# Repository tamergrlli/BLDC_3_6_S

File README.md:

# BLDC_3_6_S — Open-Source 3S–6S Sensorless BLDC Motor Driver

An open-source three-phase BLDC motor driver for 3S–6S lithium battery packs,
designed in KiCad 10. It targets sensorless six-step control using back-EMF
zero-crossing detection, with a single-shunt current sense and a hardware
over-current trip.

> **Status: work in progress.** The schematic and PCB layout are complete and
> DRC-clean; the design is in final review. The board has **not** been manufactured or tested yet. Do not order
> boards from this revision — see [Known issues](#known-issues--todo).

## Key features

| Block | Implementation |
|---|---|
| Input | 3S–6S Li-ion (≈ 9–25.2 V), SMBJ33CA TVS, polyfuse + Schottky reverse protection for the auxiliary supply |
| Power stage | 6 × TI CSD18540Q5B (60 V, SON 5×6), 2 × 22 µF ceramic per half-bridge, 2 × 330 µF bulk at the input |
| Gate driver | TI DRV8300, 12 V gate drive, separate turn-on / turn-off gate resistors |
| Current sense | 1 mΩ single DC-link shunt + INA181 (bus current, not per-phase), TLV7011 comparator wired to TIM1_BRK for a fast hardware over-current trip, 1.8 V reference (MCP1700) |
| Sensorless feedback | Per-phase back-EMF dividers with RC filter and BAT54S clamps, virtual neutral, DC-bus voltage sense |
| MCU | STM32F103R8T6, 8 MHz crystal, 5-pin SWD header with NRST, 32 Mbit SPI flash (W25Q32JV) |
| Supplies | SEPIC (LM5022) → 12 V gate drive, TPS54302 buck → 5 V, AP2112K → 3.3 V |
| Communication | CAN (TJA1042) on a Molex Micro-Fit 3.0 connector, jumper-selectable 120 Ω termination |
| User I/O | UART debug header (USART3, JST-EH), speed potentiometer, external 0–5 V analog speed input with a 5 V supply pin, 3 status LEDs, 2 push-buttons with RC debounce |
| Monitoring & debug | 12 V gate-drive rail sense, 17 test points (supply rails, BEMF, neutral, current sense, over-current trip, SPI) |
| PCB | 4 layers, 1 oz copper, 90 × 70 mm, solder-wire pads for battery (4 mm²) and motor phases (2.5 mm²) |

**Why a SEPIC?** The gate driver needs a stable 12 V rail, but a 3S pack can sag
below 12 V while a 6S pack sits well above it. A SEPIC can step up or down, so
one supply covers the whole 3S–6S range.

**Design target:** around 30 A phase current. This is a target, not a measured
value; thermal and current capability have not been verified on hardware.

## Images

| Top (3D) | Bottom (3D) |
|---|---|
|  |  |

Top copper and silkscreen: [docs/images/layout_top.png](docs/images/layout_top.png)
Schematic (PDF): [docs/BLDC_3_6_S_schematic.pdf](docs/BLDC_3_6_S_schematic.pdf)

## Repository layout

```
BLDC_3_6_S/            KiCad 10 project (schematic, PCB, design rules)
bldc_lib/symbols/      Project symbol library (DRV8300, TLV7011)
bldc_lib/3dmodels/     Vendor 3D models (not included, see README inside)
docs/                  Renders and schematic PDF
```

All project libraries are referenced relative to the project
(`${KIPRJMOD}/../bldc_lib/...`), so the design opens on any machine with
KiCad 10 and its standard libraries. Only the J4 connector's vendor 3D model has
to be downloaded separately — see [bldc_lib/3dmodels/README.md](bldc_lib/3dmodels/README.md).

## MCU pin notes

- Status LEDs: D1 on PB4, D2 on PB3, D3 on PD2.
- PB3 and PB4 are JTAG pins after reset. The firmware must disable JTAG and
  keep SWD only (CubeMX: *SYS → Debug = Serial Wire*), otherwise D1 and D2
  will not work.

## Planned hardware additions

- NTC next to the low-side MOSFETs for thermal protection
- ESD protection on the CAN bus
- RC-PWM (servo-style) speed input on a timer-capable pin, alongside the analog input

## Known issues / TODO

- [x] Move the 5 V buck switch node off the inner layer onto the top layer
- [x] Finish routing (MCU analog inputs, PWM pull-downs, SPI flash, SWD, remaining GND / 3.3 V connections)
- [ ] Route each high-side gate trace together with its phase (SH) return to shrink the gate loop
- [ ] Connect the SEPIC MOSFET snubber
- [x] Sync capacitor footprints between schematic and PCB (C28, C75, C77, C78, C80, C81 and C23, C24)
- [x] DRC clean (only silkscreen warnings remain)
- [ ] Clear ERC warnings (no-connect flags on unused MCU pins, PWR_FLAGs)
- [ ] Review copper weight (1 oz vs 2 oz) for continuous high-current operation
- [x] Add UART, speed inputs, status LEDs, push-buttons, 12 V rail sense and test points
- [ ] Add an NTC next to the power stage for thermal protection

## Roadmap

1. Finish the remaining hardware additions, complete layout, clean ERC / DRC
2. First prototype and bring-up
3. Firmware: sensorless six-step commutation with BEMF zero-crossing detection
4. Characterisation: current capability, thermals, efficiency

The board measures DC-link current only, so it is aimed at six-step control.
Field-oriented control would need per-phase current: either single-shunt
phase-current reconstruction (with a faster current-sense amplifier) or a
future hardware revision with per-phase shunts.

## Contributing

Feedback, design reviews and issues are very welcome — especially on the power
stage layout, the sensorless front end and the gate-drive loop. Please open an
issue or a pull request.

## License

This hardware design is licensed under the
**CERN Open Hardware Licence Version 2 – Strongly Reciprocal (CERN-OHL-S-2.0)**.
See [LICENSE](LICENSE) for the full text.

Copyright © 2026 tamergrlli

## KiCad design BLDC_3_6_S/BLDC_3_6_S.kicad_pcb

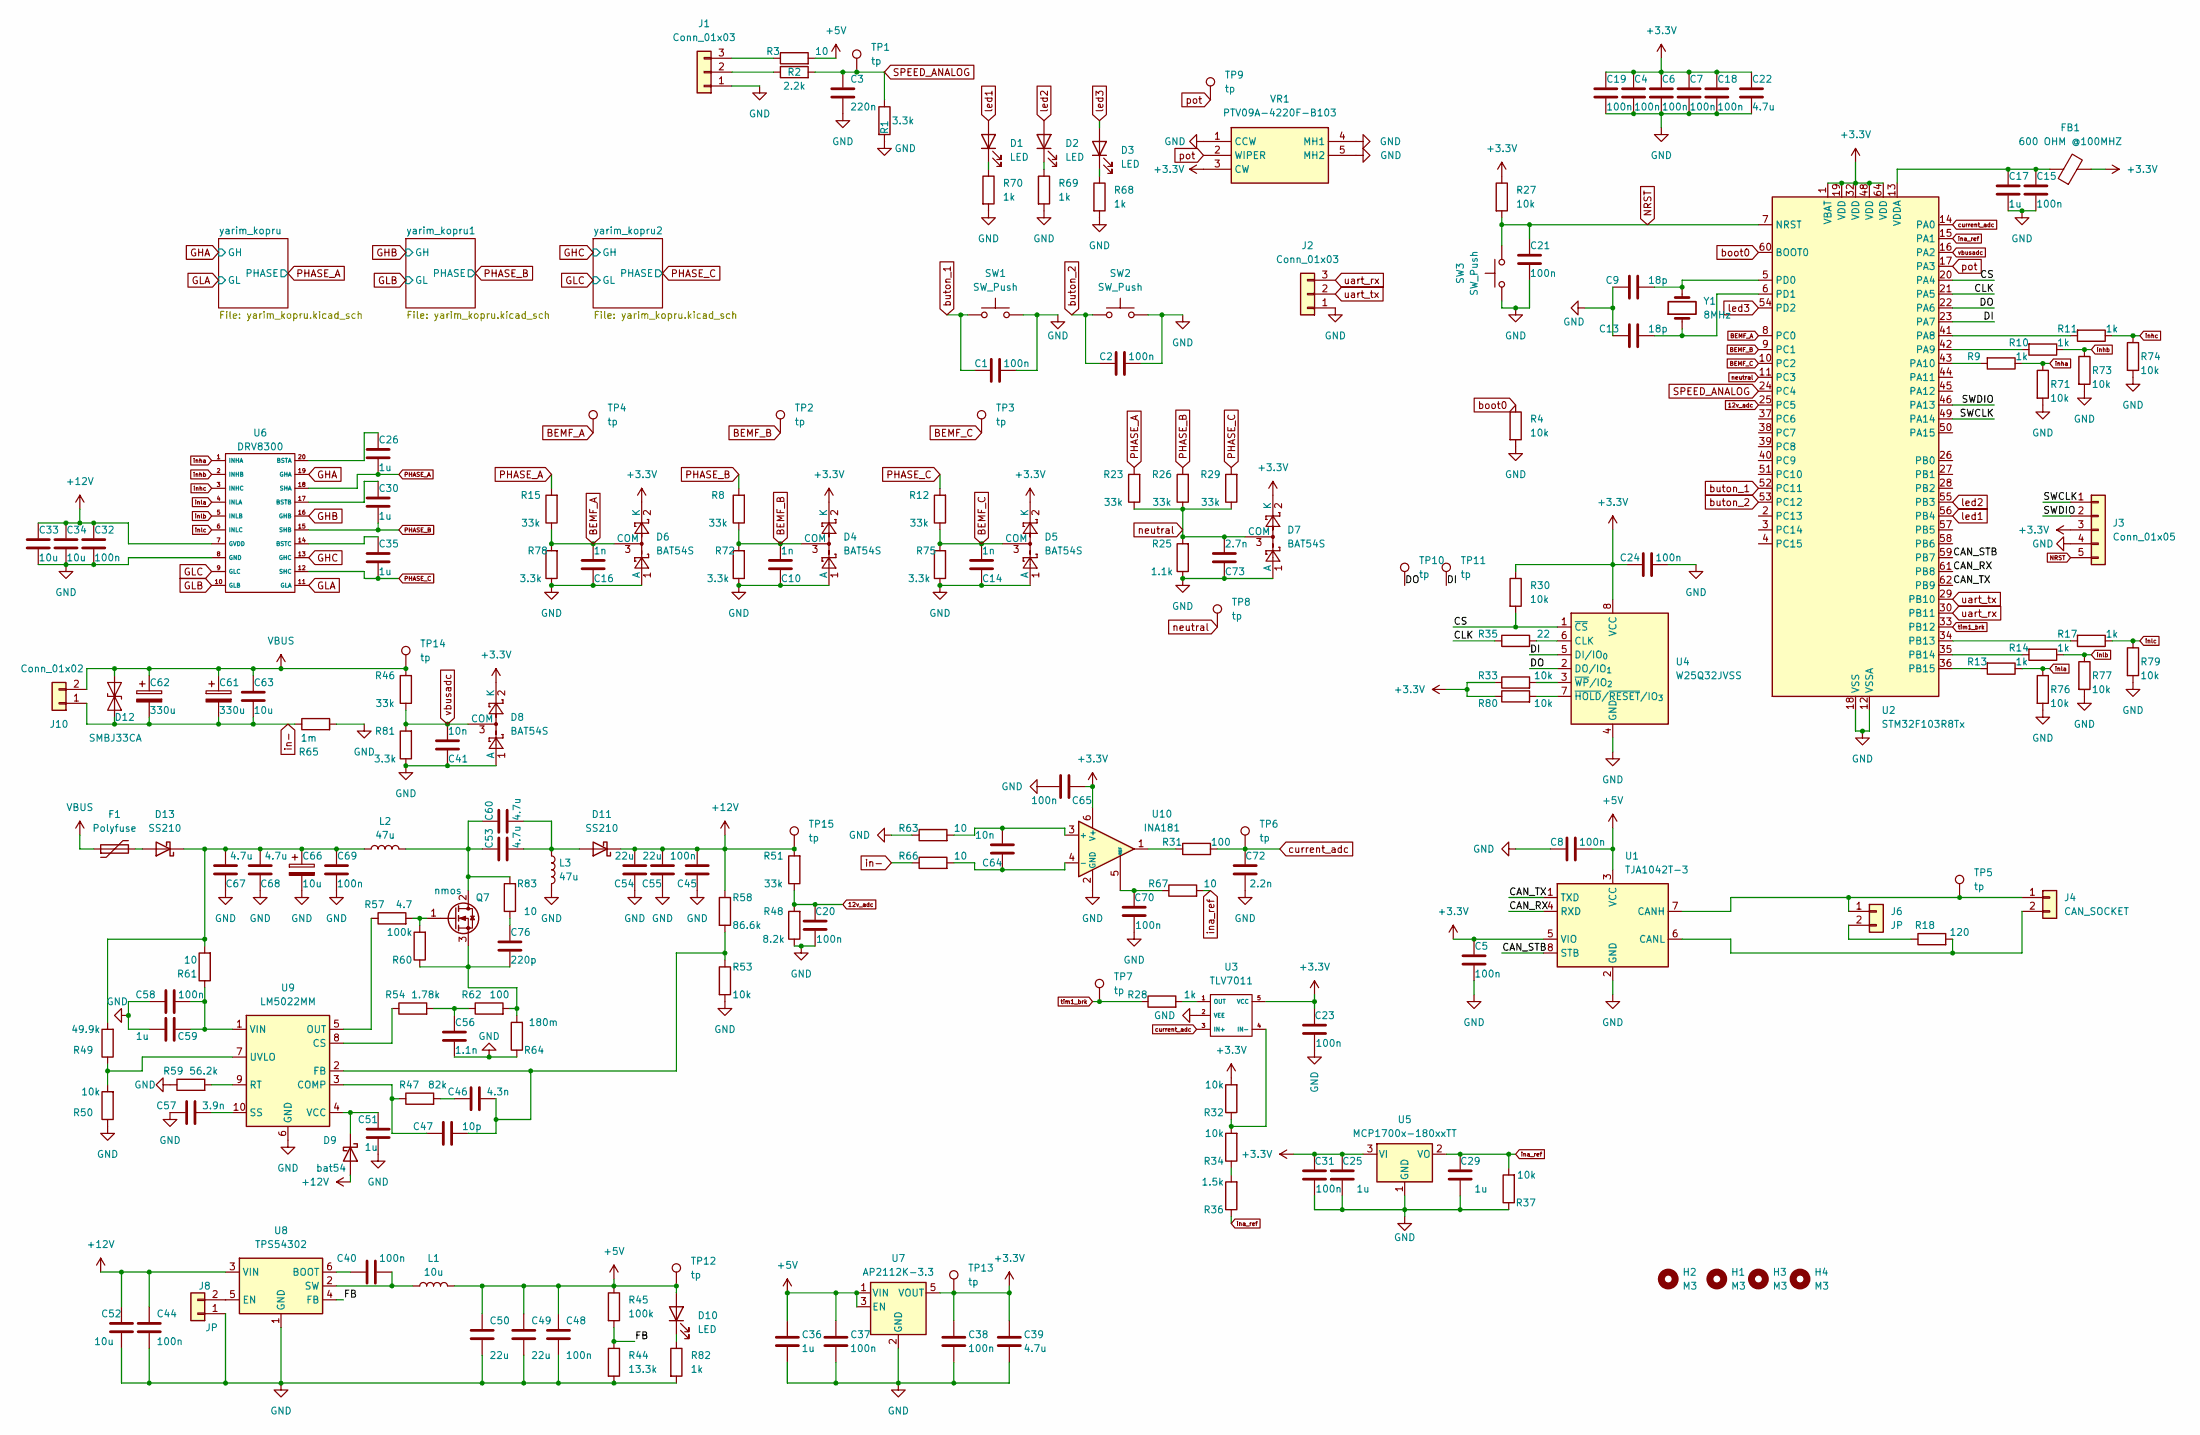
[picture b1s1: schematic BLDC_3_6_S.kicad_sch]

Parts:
C1, C2, C4, C5, C6, C7, C8, C15, C18, C19, C20, C21, C23, C24, C31, C37, C38, C45, C58, C65, C69, C70: 100n; C_0603_1608Metric
C3: 220n; C_0603_1608Metric
C9, C13: 18p; C_0603_1608Metric
C10, C14, C16: 1n; C_0603_1608Metric
C17, C25, C29: 1u; C_0603_1608Metric
C22, C39: 4.7u; C_1206_3216Metric
C26, C30, C35, C36, C51, C59: 1u; C_0805_2012Metric
C32, C40, C44, C48: 100n; C_0805_2012Metric
C33, C34: 10u; C_1210_3225Metric
C41, C64: 10n; C_0603_1608Metric
C46: 4.3n; C_0603_1608Metric
C47: 10p; C_0603_1608Metric
C49, C50: 22u; C_1206_3216Metric
C52, C63: 10u; C_1206_3216Metric
C53, C60, C67, C68: 4.7u; C_1210_3225Metric
C54, C55: 22u; C_1210_3225Metric
C56: 1.1n; C_0603_1608Metric
C57: 3.9n; C_0603_1608Metric
C61, C62: 330u; CP_Elec_10x10.5
C66: 10u; CP_Elec_6.3x5.3
C72: 2.2n; C_0603_1608Metric
C73: 2.7n; C_0603_1608Metric
C76: 220p; C_0603_1608Metric
D1, D2, D3, D10: LED; LED_0805_2012Metric
D4, D5, D6, D7, D8: BAT54S; SOT-23
D9: bat54; D_SOD-123
D11, D13: SS210; D_SMA
D12: SMBJ33CA; D_SMB
F1: Polyfuse; R_1812_4532Metric
FB1: 600 OHM @100MHZ; L_0805_2012Metric
H1, H2, H3, H4: M3; MountingHole_3.2mm_M3_ISO7380
J1, J2: Conn_01x03; JST_EH_B3B-EH-A_1x03_P2.50mm_Vertical
J3: Conn_01x05; PinHeader_1x05_P2.54mm_Vertical
J4: CAN_SOCKET; Molex_Micro-Fit_3.0_43650-0200_1x02_P3.00mm_Horizontal
J6, J8: JP; PinHeader_1x02_P1.27mm_Vertical
J10: Conn_01x02; SolderWire-4sqmm_1x02_P12mm_D3mm_OD6mm
L1: 10u; L_Bourns-SRN4018
L2, L3: 47u; L_Bourns_SRR1260
Q7: nmos; TO-252-2
R1, R72, R75, R78, R81: 3.3k; R_0603_1608Metric
R2: 2.2k; R_0603_1608Metric
R3, R61, R63, R66, R67, R83: 10; R_0603_1608Metric
R4, R27, R30, R32, R33, R34, R37, R50, R53, R71, R73, R74, R76, R77, R79, R80: 10k; R_0603_1608Metric
R8, R12, R15, R23, R26, R29, R46, R51: 33k; R_0603_1608Metric
R9, R10, R11, R13, R14, R17, R28: 1k; R_0603_1608Metric
R18: 120; R_0603_1608Metric
R25: 1.1k; R_0603_1608Metric
R31, R62: 100; R_0603_1608Metric
R35: 22; R_0805_2012Metric
R36: 1.5k; R_0603_1608Metric
R44: 13.3k; R_0805_2012Metric
R45: 100k; R_0805_2012Metric
R47: 82k; R_0603_1608Metric
R48: 8.2k; R_0603_1608Metric
R49: 49.9k; R_0603_1608Metric
R54: 1.78k; R_0603_1608Metric
R57: 4.7; R_0603_1608Metric
R58: 86.6k; R_0603_1608Metric
R59: 56.2k; R_0603_1608Metric
R60: 100k; R_0603_1608Metric
R64: 180m; R_1206_3216Metric
R65: 1m; R_2512_6332Metric
R68, R69, R70, R82: 1k; R_0805_2012Metric
SW1, SW2, SW3: SW_Push; SW_Push_1P1T_NO_CK_KMR2
TP1, TP2, TP3, TP4, TP5, TP6, TP7, TP8, TP9, TP10, TP11, TP12, TP13, TP14, TP15: tp; TestPoint_Pad_D1.5mm
U1: TJA1042T-3; SOIC-8_3.9x4.9mm_P1.27mm
U2: STM32F103R8Tx; LQFP-64_10x10mm_P0.5mm
U3: TLV7011; SOT-23-5
U4: W25Q32JVSS; SOIC-8_5.3x5.3mm_P1.27mm
U5: MCP1700x-180xxTT; SOT-23
U6: DRV8300; TSSOP-20_4.4x6.5mm_P0.65mm
U7: AP2112K-3.3; SOT-23-5
U8: TPS54302; SOT-23-6
U9: LM5022MM; MSOP-10_3x3mm_P0.5mm
U10: INA181; SOT-23-6
VR1: PTV09A-4220F-B103; PTV09A4220FB103; Mouser Part Number 652-PTV09A-4220FB103
Y1: 8MHz; Crystal_SMD_5032-2Pin_5.0x3.2mm

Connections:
12v_adc: C20.2, R48.2, R51.1, U2.25 (PC5)
+3.3V: C4.2, C5.1, C6.2, C7.2, C18.2, C19.2, C22.2, C23.2, C24.1, C25.2, C31.2, C38.2, C39.1, C65.2, D4.2 (K), D5.2 (K), D6.2 (K), D7.2 (K), D8.2 (K), FB1.2, J3.3, R27.1, R30.1, R32.2, R33.1, R80.1, TP13.1 (1_1), U1.5 (VIO), U2.1 (VBAT), U2.19 (VDD), U2.32 (VDD), U2.48 (VDD), U2.64 (VDD), U3.5 (VCC), U4.8 (VCC), U5.3 (VI), U7.5 (VOUT), U10.6 (V+), VR1.3 (CW)
+5V: C8.2, C36.1, C37.2, C48.1, C49.1, C50.1, D10.2 (A), L1.2, R3.2, R45.1, TP12.1 (1_1), U1.3 (VCC), U7.1 (VIN), U7.3 (EN)
+12V: C32.1, C33.1, C34.1, C44.1, C45.1, C52.1, C54.2, C55.2, D9.2 (A), D11.1 (K), R51.2, R58.1, TP15.1 (1_1), U6.7 (GVDD), U8.3 (VIN)
/CAN_RX: U1.4 (RXD), U2.61 (PB8)
/CAN_STB: U1.8 (STB), U2.59 (PB7)
/CAN_TX: U1.1 (TXD), U2.62 (PB9)
/CLK: R35.1, U2.21 (PA5)
/CS: R30.2, U2.20 (PA4), U4.1 (~CS)
/DI: TP11.1 (1_1), U2.23 (PA7), U4.5 (DI/IO_{0})
/DO: TP10.1 (1_1), U2.22 (PA6), U4.2 (DO/IO_{1})
/FB: R44.1, R45.2, U8.4 (FB)
/SWCLK: J3.1, U2.49 (PA14)
/SWDIO: J3.2, U2.46 (PA13)
BEMF_A: C16.1, D6.3 (COM), R15.1, R78.2, TP4.1 (1_1), U2.8 (PC0)
BEMF_B: C10.1, D4.3 (COM), R8.1, R72.2, TP2.1 (1_1), U2.9 (PC1)
BEMF_C: C14.1, D5.3 (COM), R12.1, R75.2, TP3.1 (1_1), U2.10 (PC2)
GHA: U6.19 (GHA); also elsewhere on the board
GHB: U6.16 (GHB); also elsewhere on the board
GHC: U6.13 (GHC); also elsewhere on the board
GLA: U6.11 (GLA); also elsewhere on the board
GLB: U6.10 (GLB); also elsewhere on the board
GLC: U6.9 (GLC); also elsewhere on the board
GND: C1.2, C2.2, C3.2, C4.1, C5.2, C6.1, C7.1, C8.1, C9.1, C10.2, C13.1, C14.2, C15.1, C16.2, C17.1, C18.1, C19.1, C20.1, C21.2, C22.1, C23.1, C24.2, C25.1, C29.1, C31.1, C32.2, C33.2, C34.2, C36.2, C37.1, C38.1, C39.2, C41.2, C44.2, C45.2, C48.2, C49.2, C50.2, C51.2, C52.2, C54.1, C55.1, C56.2, C57.1, C58.1, C59.2, C65.1, C66.2, C67.1, C68.1, C69.2, C70.1, C72.1, C73.2, D4.1 (A), D5.1 (A), D6.1 (A), D7.1 (A), D8.1 (A), J1.1, J2.1, J3.4, J8.1, L3.2, R1.2, R4.2, R25.1, R37.1, R44.2, R48.1, R50.1, R53.2, R59.1, R63.1, R64.1, R65.2, R68.2, R69.2, R70.2, R71.2, R72.1, R73.2, R74.2, R75.1, R76.2, R77.2, R78.1, R79.2, R81.1, R82.2, SW1.2, SW2.2, SW3.1, U1.2 (GND), U2.12 (VSSA), U2.18 (VSS), U2.31 (VSS), U2.47 (VSS), U2.63 (VSS), U3.2 (VEE), U4.4 (GND), U5.1 (GND), U6.8 (GND), U7.2 (GND), U8.1 (GND), U9.6 (GND), U10.2 (GND), VR1.1 (CCW), VR1.4 (MH1), VR1.5 (MH2); also elsewhere on the board
NRST: C21.1, J3.5, R27.2, SW3.2, U2.7 (NRST)
unnamed: C46.1, R47.2
unnamed: C56.1, R54.2, R62.1
unnamed: C76.1, R83.1
unnamed: D1.1 (K), R70.1
unnamed: D2.1 (K), R69.1
unnamed: D3.1 (K), R68.1
unnamed: C51.1, D9.1 (K), U9.4 (VCC)
unnamed: D10.1 (K), R82.1
unnamed: C53.2, C60.2, D11.2 (A), L3.1
unnamed: D13.2 (A), F1.2
unnamed: C66.1, C67.2, C68.2, C69.1, D13.1 (K), L2.1, R49.2, R61.2
unnamed: J1.2, R2.1
unnamed: J1.3, R3.1
unnamed: J4.1, J6.1, TP5.1 (1_1), U1.7 (CANH)
unnamed: J4.2, R18.2, U1.6 (CANL)
unnamed: J6.2, R18.1
unnamed: J8.2, U8.5 (EN)
unnamed: C53.1, C60.1, L2.2, Q7.2 (D), R83.2
unnamed: Q7.1 (G), R57.2, R60.2
unnamed: C76.2, Q7.3 (S), R60.1, R62.2, R64.2
unnamed: R31.1, U10.1
unnamed: R34.1, R36.2
unnamed: R11.2, U2.41 (PA8)
unnamed: R10.2, U2.42 (PA9)
unnamed: R9.2, U2.43 (PA10)
unnamed: R17.2, U2.34 (PB13)
unnamed: R14.2, U2.35 (PB14)
unnamed: R13.2, U2.36 (PB15)
unnamed: C9.2, U2.5 (PD0), Y1.2
unnamed: C13.2, U2.6 (PD1), Y1.1
unnamed: C15.2, C17.2, FB1.1, U2.13 (VDDA)
unnamed: R32.1, R34.2, U3.4 (IN-)
unnamed: R28.2, U3.1 (OUT)
unnamed: R35.2, U4.6 (CLK)
unnamed: R80.2, U4.7 (~HOLD/~RESET/IO_{3})
unnamed: R33.2, U4.3 (~WP/IO_{2})
unnamed: C26.1, U6.20 (BSTA)
unnamed: C30.1, U6.17 (BSTB)
unnamed: C35.1, U6.14 (BSTC)
unnamed: C40.1, U8.6 (BOOT)
unnamed: C40.2, L1.1, U8.2 (SW)
unnamed: C47.1, R47.1, U9.3 (COMP)
unnamed: R54.1, U9.8 (CS)
unnamed: C46.2, C47.2, R53.1, R58.2, U9.2 (FB)
unnamed: R57.1, U9.5 (OUT)
unnamed: R59.2, U9.9 (RT)
unnamed: C57.2, U9.10 (SS)
unnamed: R49.1, R50.2, U9.7 (UVLO)
unnamed: C58.2, C59.1, R61.1, U9.1 (VIN)
unnamed: C64.1, R63.2, U10.3 (+)
unnamed: C64.2, R66.2, U10.4 (-)
unnamed: C70.2, R67.1, U10.5 (REF)
PHASE_A: C26.2, R15.2, R23.2, U6.18 (SHA); also elsewhere on the board
PHASE_B: C30.2, R8.2, R26.2, U6.15 (SHB); also elsewhere on the board
PHASE_C: C35.2, R12.2, R29.2, U6.12 (SHC); also elsewhere on the board
SPEED_ANALOG: C3.1, R1.1, R2.2, TP1.1 (1_1), U2.24 (PC4)
VBUS: C61.1, C62.1, C63.1, D12.1 (A1), F1.1, J10.2, R46.2, TP14.1 (1_1); also elsewhere on the board
boot0: R4.1, U2.60 (BOOT0)
buton_1: C1.1, SW1.1, U2.52 (PC11)
buton_2: C2.1, SW2.1, U2.53 (PC12)
current_adc: C72.2, R31.2, TP6.1 (1_1), U2.14 (PA0), U3.3 (IN+)
in-: C61.2, C62.2, C63.2, D12.2 (A2), J10.1, R65.1, R66.1
ina_ref: C29.2, R36.1, R37.2, R67.2, U2.15 (PA1), U5.2 (VO)
inha: R9.1, R71.1, U6.1 (INHA)
inhb: R10.1, R73.1, U6.2 (INHB)
inhc: R11.1, R74.1, U6.3 (INHC)
inla: R13.1, R76.1, U6.4 (INLA)
inlb: R14.1, R77.1, U6.5 (INLB)
inlc: R17.1, R79.1, U6.6 (INLC)
led1: D1.2 (A), U2.56 (PB4)
led2: D2.2 (A), U2.55 (PB3)
led3: D3.2 (A), U2.54 (PD2)
neutral: C73.1, D7.3 (COM), R23.1, R25.2, R26.1, R29.1, TP8.1 (1_1), U2.11 (PC3)
pot: TP9.1 (1_1), U2.17 (PA3), VR1.2 (WIPER)
tim1_brk: R28.1, TP7.1 (1_1), U2.33 (PB12)
uart_rx: J2.3, U2.30 (PB11)
uart_tx: J2.2, U2.29 (PB10)
vbusadc: C41.1, D8.3 (COM), R46.1, R81.2, U2.16 (PA2)

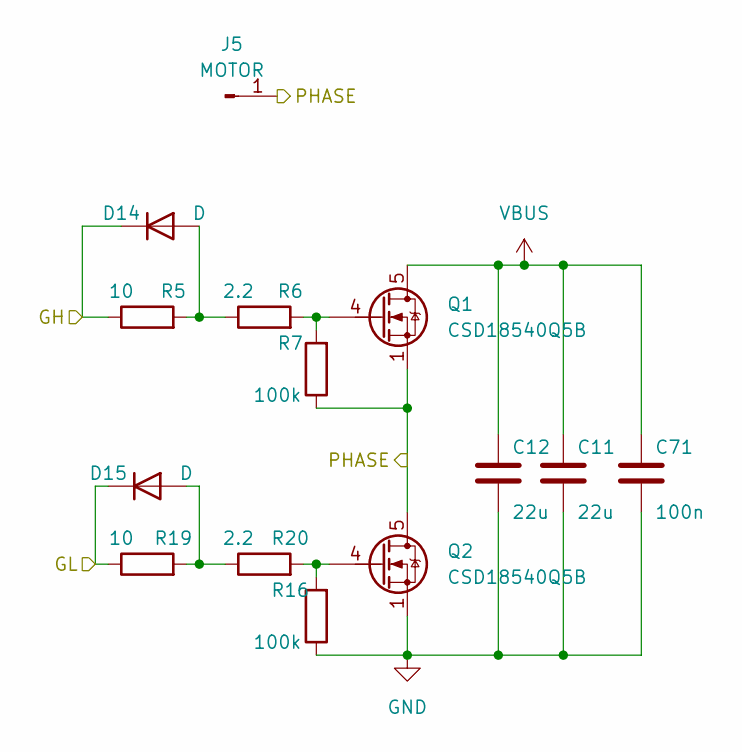
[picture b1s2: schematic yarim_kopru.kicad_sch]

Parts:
C11, C12: 22u; C_1210_3225Metric
C71: 100n; C_0805_2012Metric
D14, D15: D; D_SOD-123
J5: MOTOR; SolderWire-2.5sqmm_1x01_D2.4mm_OD4.4mm
Q1, Q2: CSD18540Q5B; TDSON-8-1
R5, R19: 10; R_0603_1608Metric
R6, R20: 2.2; R_0603_1608Metric
R7, R16: 100k; R_0603_1608Metric

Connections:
GHA: D14.1 (K), R5.1; also elsewhere on the board
GLA: D15.1 (K), R19.1; also elsewhere on the board
GND: C11.2, C12.2, C71.2, Q2.1 (S), Q2.2 (S), Q2.3 (S), R16.1; also elsewhere on the board
unnamed: D14.2 (A), R5.2, R6.1
unnamed: D15.2 (A), R19.2, R20.1
unnamed: Q1.4 (G), R6.2, R7.2
unnamed: Q2.4 (G), R16.2, R20.2
PHASE_A: J5.1 (Pin_1_1), Q1.1 (S), Q1.2 (S), Q1.3 (S), Q2.5 (D), R7.1; also elsewhere on the board
VBUS: C11.1, C12.1, C71.1, Q1.5 (D); also elsewhere on the board

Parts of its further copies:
C27, C28, C42, C43: 22u; C_1210_3225Metric
C74, C75: 100n; C_0805_2012Metric
D16, D17, D18, D19: D; D_SOD-123
J7, J9: MOTOR; SolderWire-2.5sqmm_1x01_D2.4mm_OD4.4mm
Q3, Q4, Q5, Q6: CSD18540Q5B; TDSON-8-1
R21, R39, R41, R55: 10; R_0603_1608Metric
R22, R40, R42, R56: 2.2; R_0603_1608Metric
R24, R38, R43, R52: 100k; R_0603_1608Metric

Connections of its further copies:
GHB: D16.1 (K), R21.1; also elsewhere on the board
GHC: D18.1 (K), R41.1; also elsewhere on the board
GLB: D17.1 (K), R39.1; also elsewhere on the board
GLC: D19.1 (K), R55.1; also elsewhere on the board
GND: C27.2, C28.2, C42.2, C43.2, C74.2, C75.2, Q4.1 (S), Q4.2 (S), Q4.3 (S), Q6.1 (S), Q6.2 (S), Q6.3 (S), R38.1, R52.1; also elsewhere on the board
unnamed: D16.2 (A), R21.2, R22.1
unnamed: D17.2 (A), R39.2, R40.1
unnamed: D18.2 (A), R41.2, R42.1
unnamed: D19.2 (A), R55.2, R56.1
unnamed: Q3.4 (G), R22.2, R24.2
unnamed: Q4.4 (G), R38.2, R40.2
unnamed: Q5.4 (G), R42.2, R43.2
unnamed: Q6.4 (G), R52.2, R56.2
PHASE_B: J7.1 (Pin_1_1), Q3.1 (S), Q3.2 (S), Q3.3 (S), Q4.5 (D), R24.1; also elsewhere on the board
PHASE_C: J9.1 (Pin_1_1), Q5.1 (S), Q5.2 (S), Q5.3 (S), Q6.5 (D), R43.1; also elsewhere on the board
VBUS: C27.1, C28.1, C42.1, C43.1, C74.1, C75.1, Q3.5 (D), Q5.5 (D); also elsewhere on the board

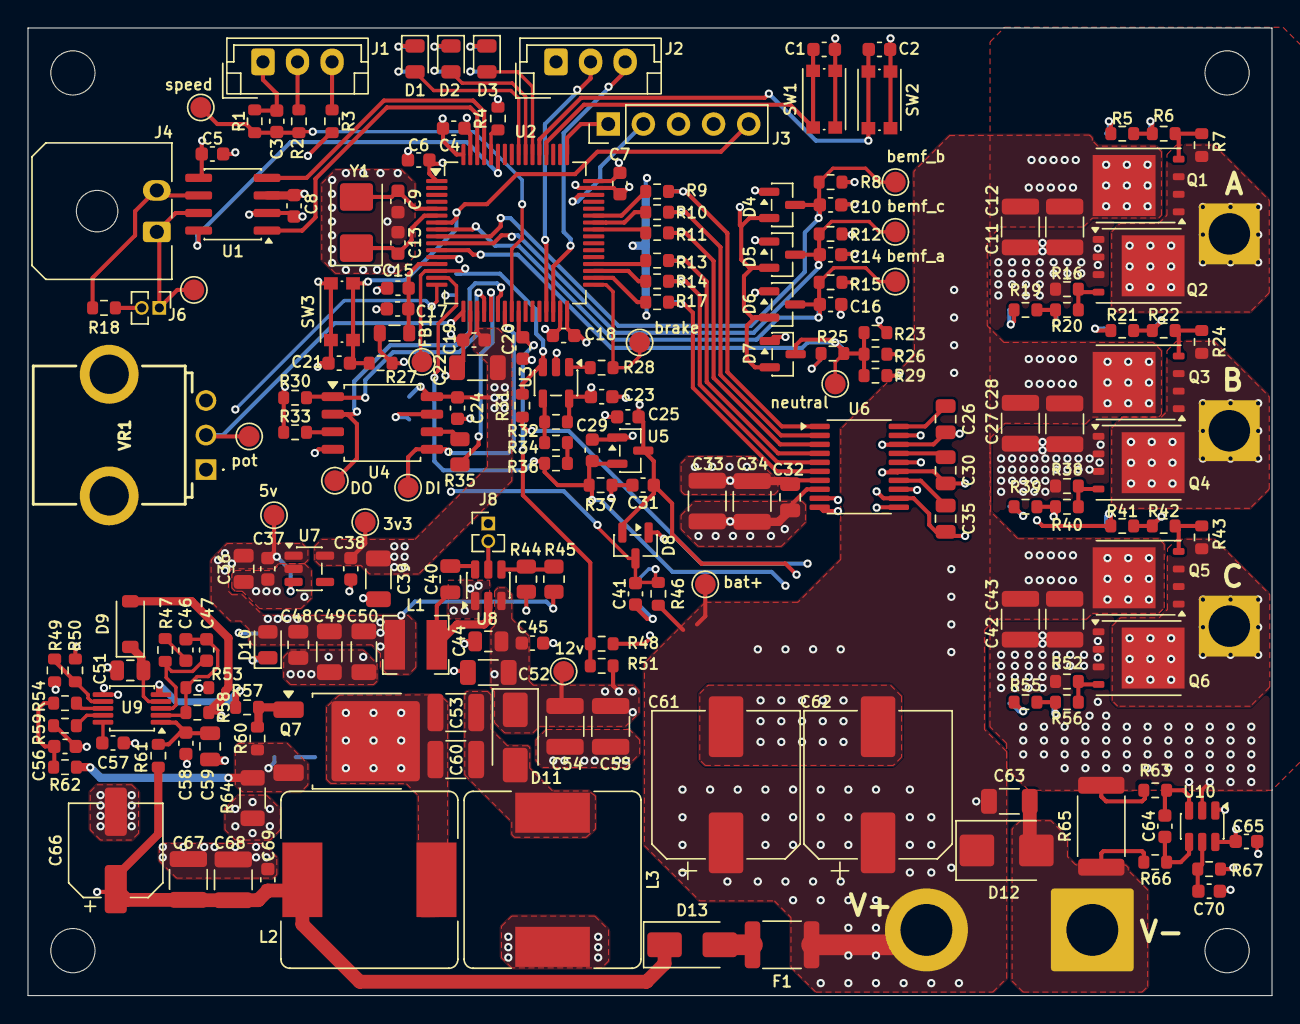
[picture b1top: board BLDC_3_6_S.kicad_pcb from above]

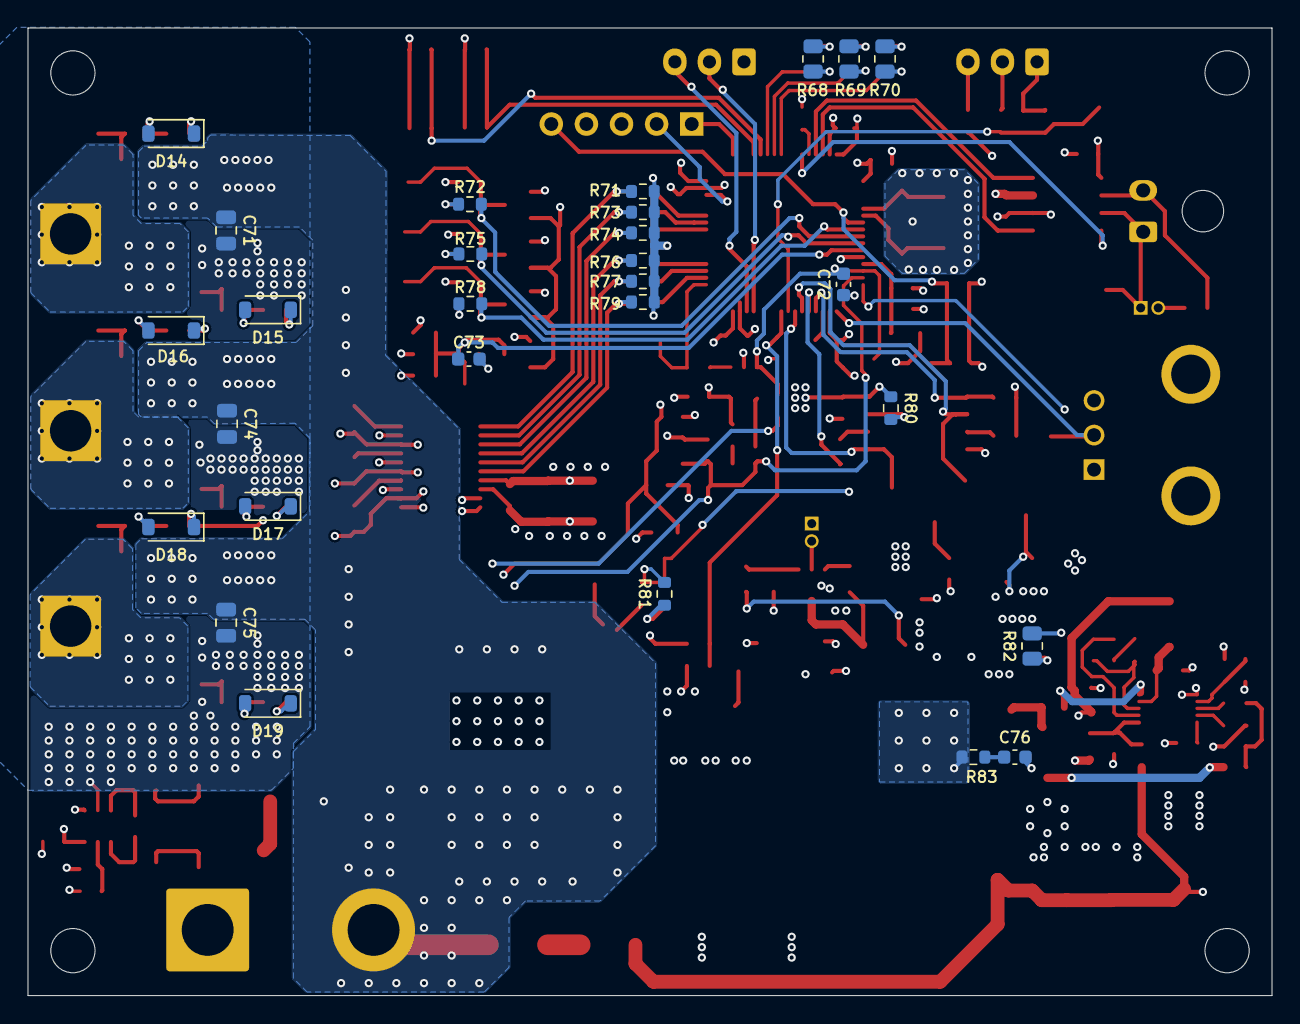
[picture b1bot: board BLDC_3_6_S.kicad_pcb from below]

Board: 4 copper layers, 90.0 x 70.0 mm, 234 parts (28 on the bottom side), 115 nets.
